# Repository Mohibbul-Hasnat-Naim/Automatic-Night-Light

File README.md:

# Automatic-Night-Light
This circuit, created using the NE555 timer, automatically switches lights on and off in response to changes in daylight and darkness.

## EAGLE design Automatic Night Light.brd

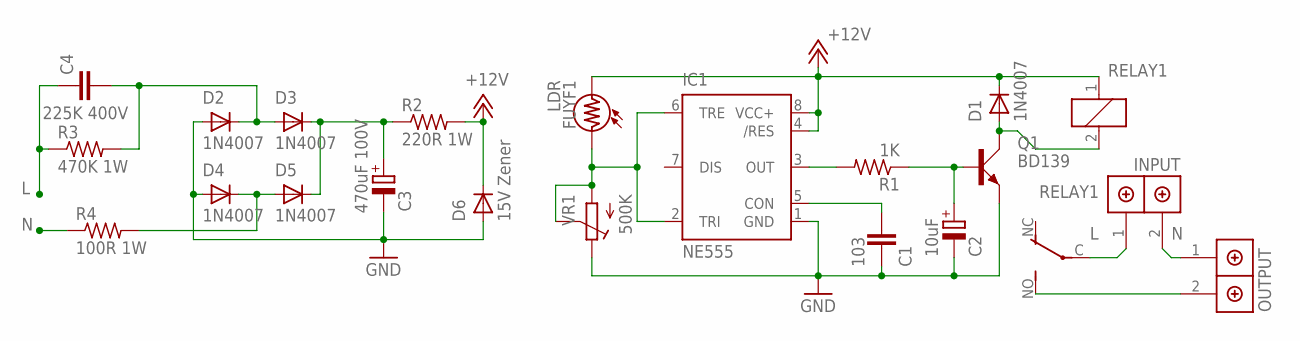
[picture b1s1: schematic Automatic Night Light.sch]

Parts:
C1: 103; 104
C2: 10uF; 10UF/50V
C3: 470uF 100V; 1000UF/16V
C4: 225K 400V; C150-091X182
D1, D2, D3, D4, D5: 1N4007; 1N4007_V2
D6: 15V Zener; 1N4007_V2
FUYF1: LDR
IC1: NE555; DIL-08
INPUT: INPUT; 2P
OUTPUT: 2P
Q1: BD139; TO126AV
R1: 1K; THR_R_204/7
R2: 220R 1W; 1/2W
R3: 470K 1W; 1/2W
R4: 100R 1W; 1/2W
RELAY1: RELAY
VR1: 500K; BLUE_VR

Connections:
+12V: D1.C, D6.C, FUYF1.3, IC1.4 (/RES), IC1.8 (VCC+), R2.2, RELAY1.1
GND: C1.2, C2.-, C3.-, D2.A, D4.A, D6.A, IC1.1 (GND), Q1.E, VR1.1
L: C4.1, INPUT.1 (CONN1), R3.1, RELAY1.C
N: INPUT.2 (CONN2), OUTPUT.1 (CONN1), R4.1
unnamed: C1.1, IC1.5 (CON)
unnamed: IC1.3 (OUT), R1.2
unnamed: FUYF1.1, IC1.2 (TRI), IC1.6 (TRE), VR1.2, VR1.3
unnamed: C2.+, Q1.B, R1.1
unnamed: D1.A, Q1.C, RELAY1.2
unnamed: C4.2, D2.C, D3.A, R3.2
unnamed: OUTPUT.2 (CONN2), RELAY1.NO
unnamed: C3.+, D3.C, D5.C, R2.1
unnamed: D4.C, D5.A, R4.2

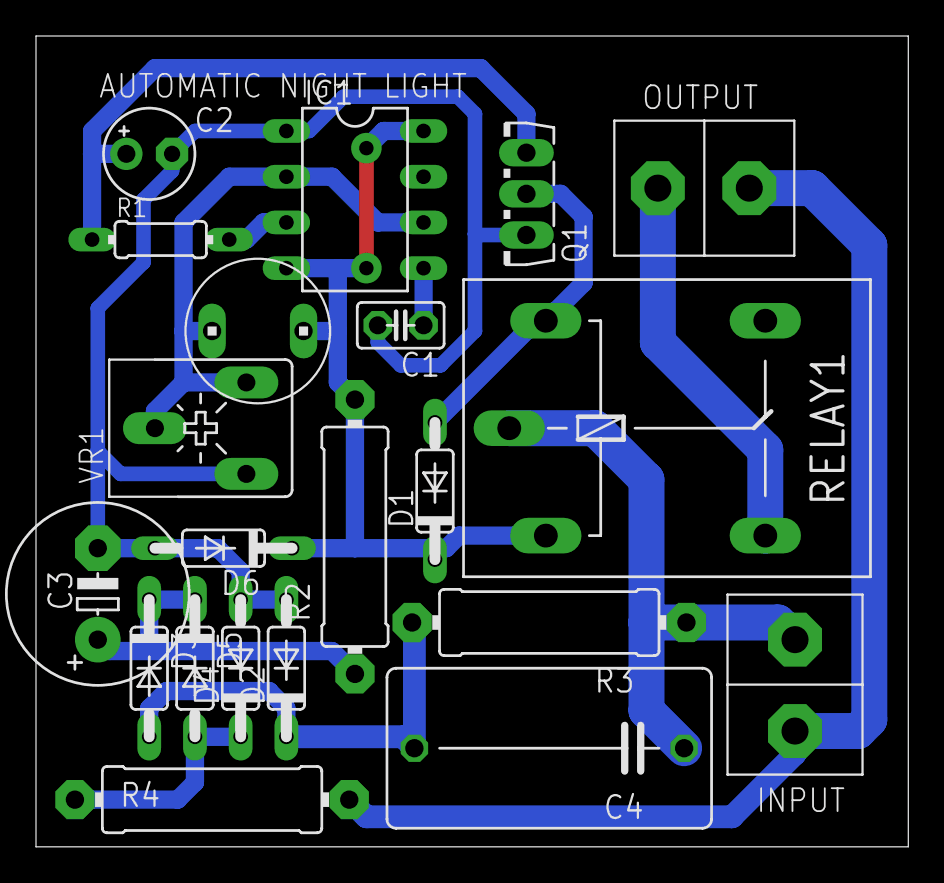
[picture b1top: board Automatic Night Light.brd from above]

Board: 2 copper layers, 48.5 x 45.0 mm, 21 parts (0 on the bottom side), 13 nets.
